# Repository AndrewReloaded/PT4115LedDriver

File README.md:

# PT4115LedDriver
PT4115 Led Driver

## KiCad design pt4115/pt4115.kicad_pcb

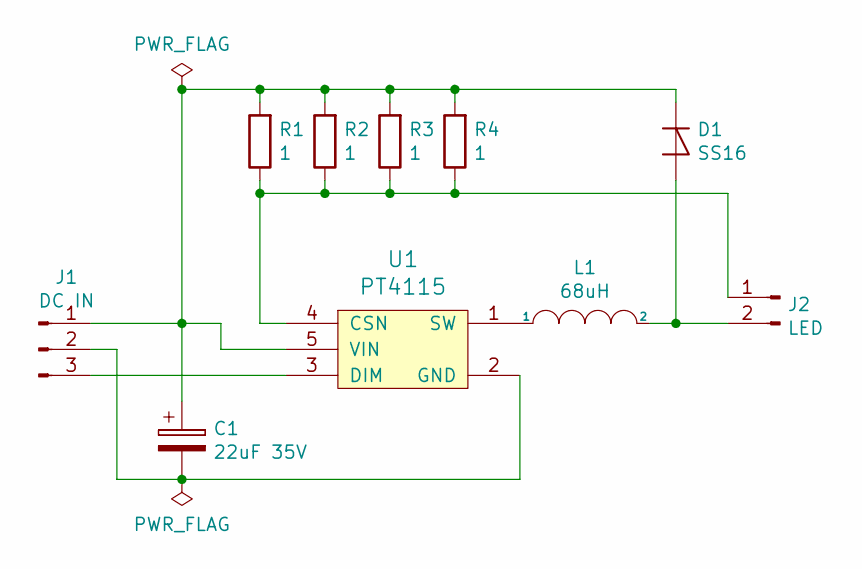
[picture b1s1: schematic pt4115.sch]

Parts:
C1: 22uF 35V; CP_EIA-7343-31_Kemet-D
D1: SS16; D_SMA
J1: DC IN; SolderWirePad_1x03_P3.175mm_Drill0.8mm
J2: LED; SolderWirePad_1x02_P3.81mm_Drill0.8mm
L1: 68uH; L_6.3x6.3_H3
R1, R2, R3, R4: 1; R_1206_3216Metric
U1: PT4115; SOT89-5_Housing

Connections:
unnamed: C1.1, D1.1 (K), J1.1, R1.2, R2.2, R3.2, R4.2, U1.5 (VIN)
unnamed: C1.2, J1.2, U1.2 (GND)
unnamed: D1.2 (A), J2.2, L1.2
unnamed: J1.3, U1.3 (DIM)
unnamed: J2.1, R1.1, R2.1, R3.1, R4.1, U1.4 (CSN)
unnamed: L1.1, U1.1 (SW)

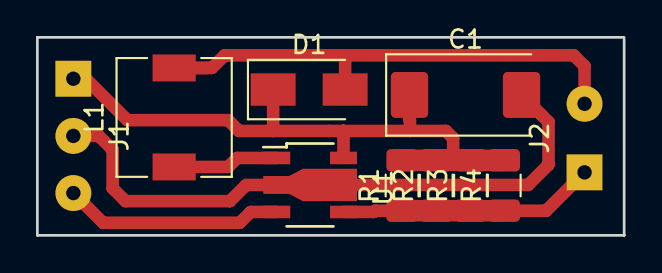
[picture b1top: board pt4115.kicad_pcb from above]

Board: 2 copper layers, 32.6 x 11.0 mm, 10 parts (0 on the bottom side), 6 nets.

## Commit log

2019-02-08 Pcb updated
